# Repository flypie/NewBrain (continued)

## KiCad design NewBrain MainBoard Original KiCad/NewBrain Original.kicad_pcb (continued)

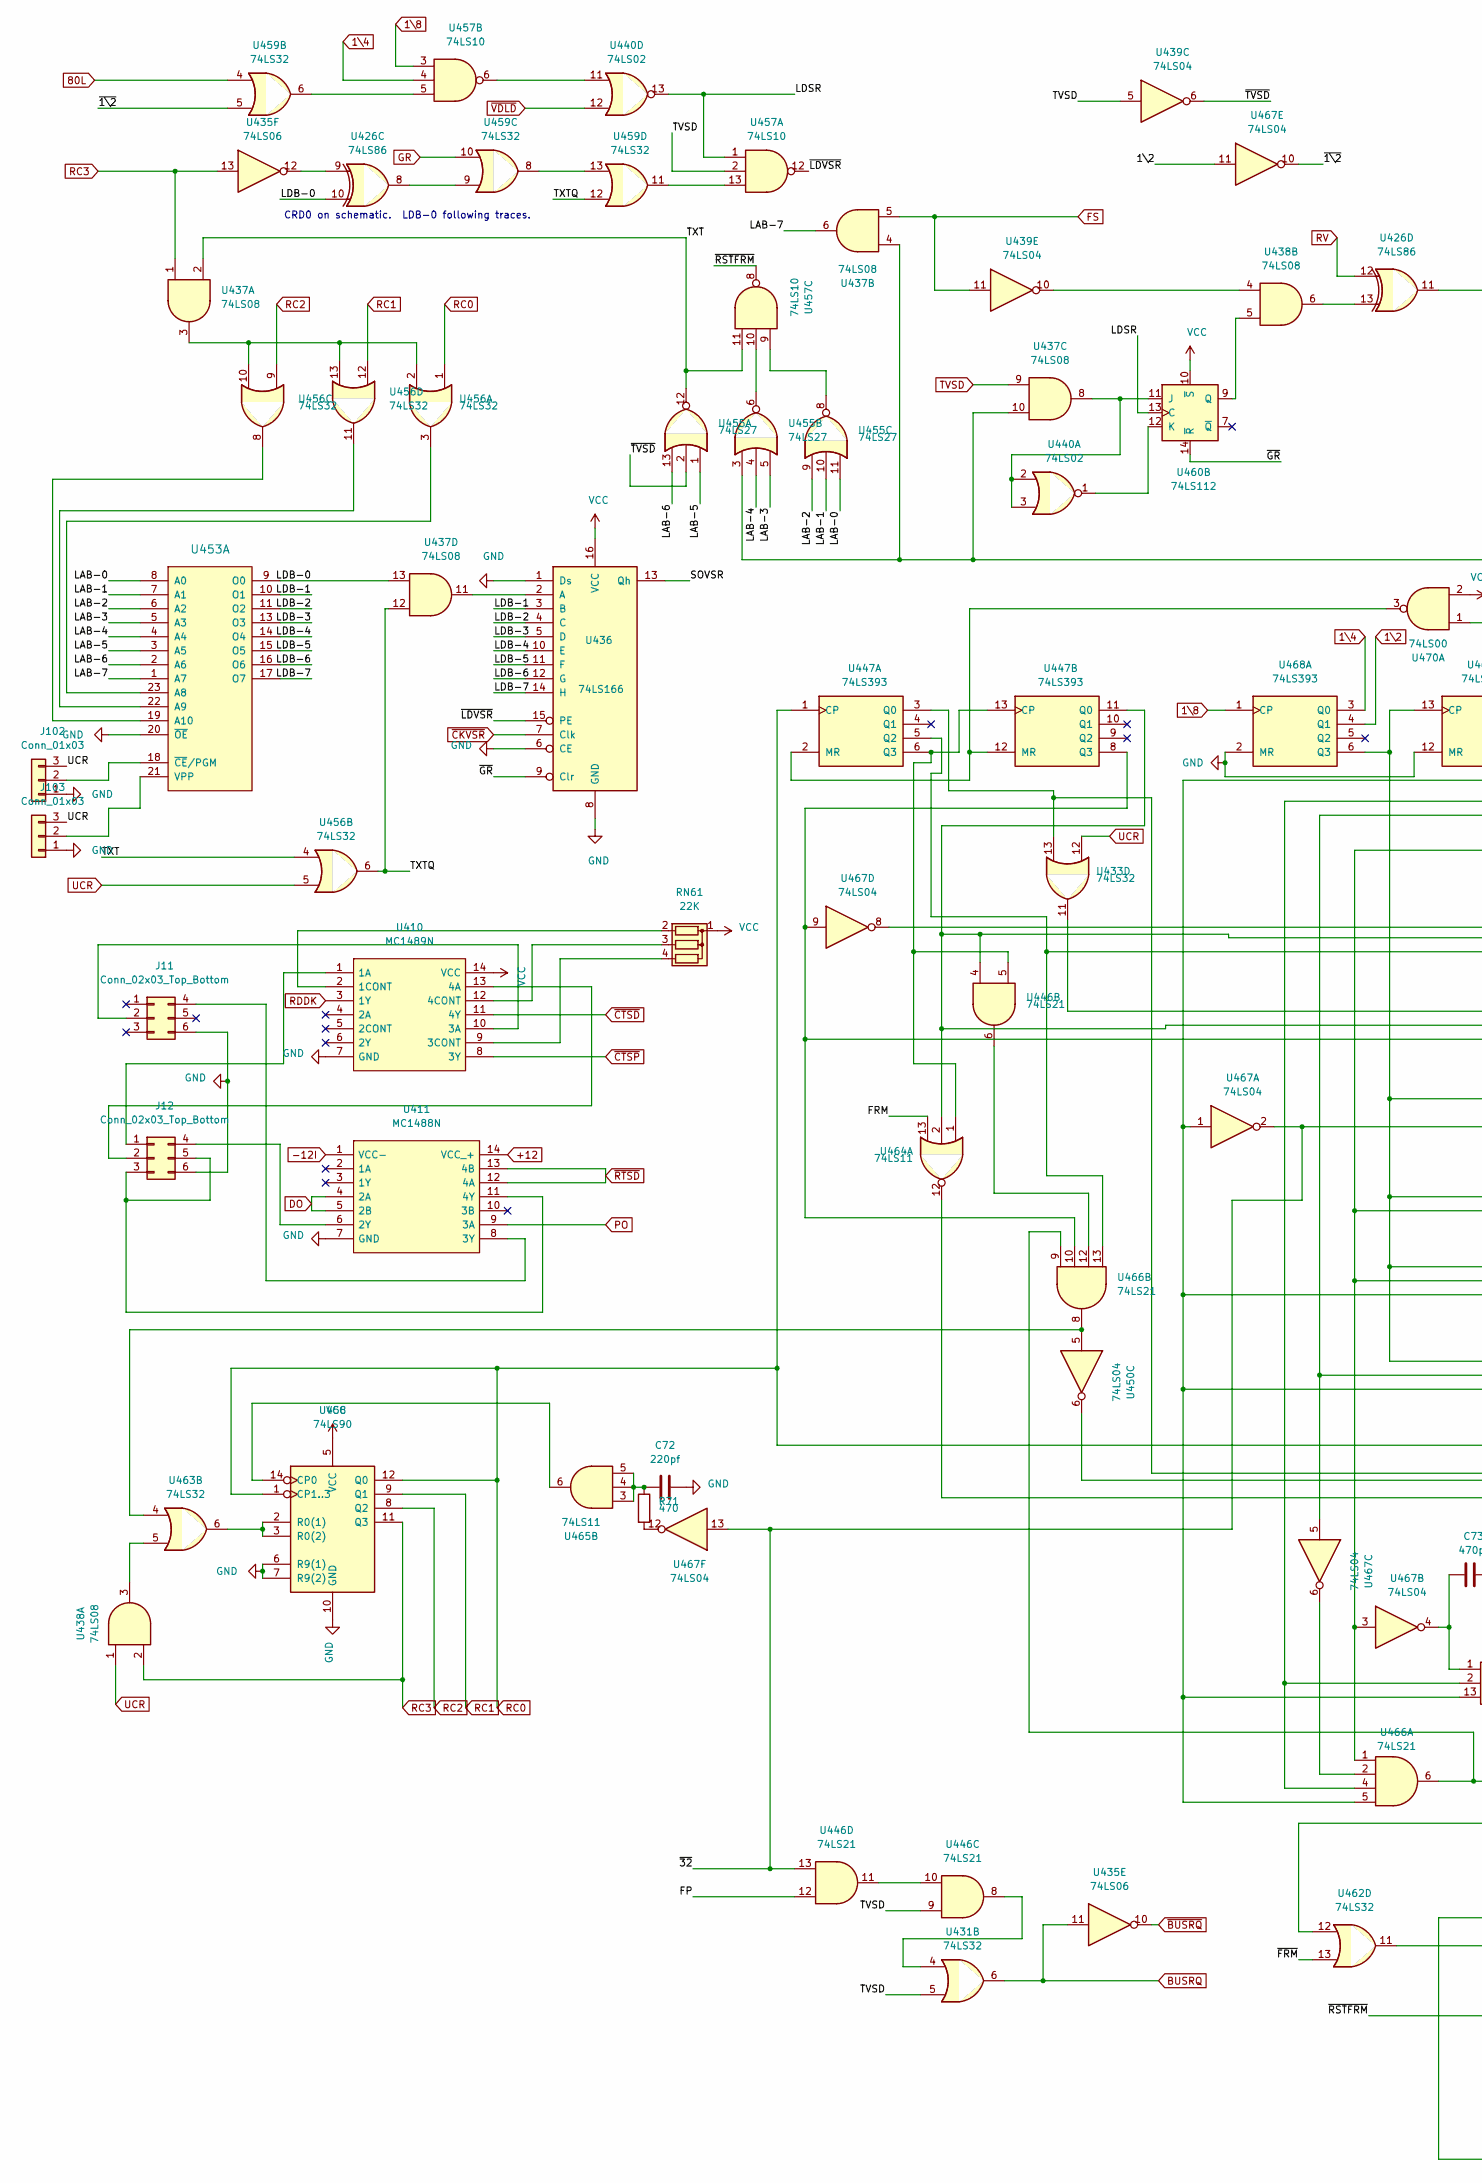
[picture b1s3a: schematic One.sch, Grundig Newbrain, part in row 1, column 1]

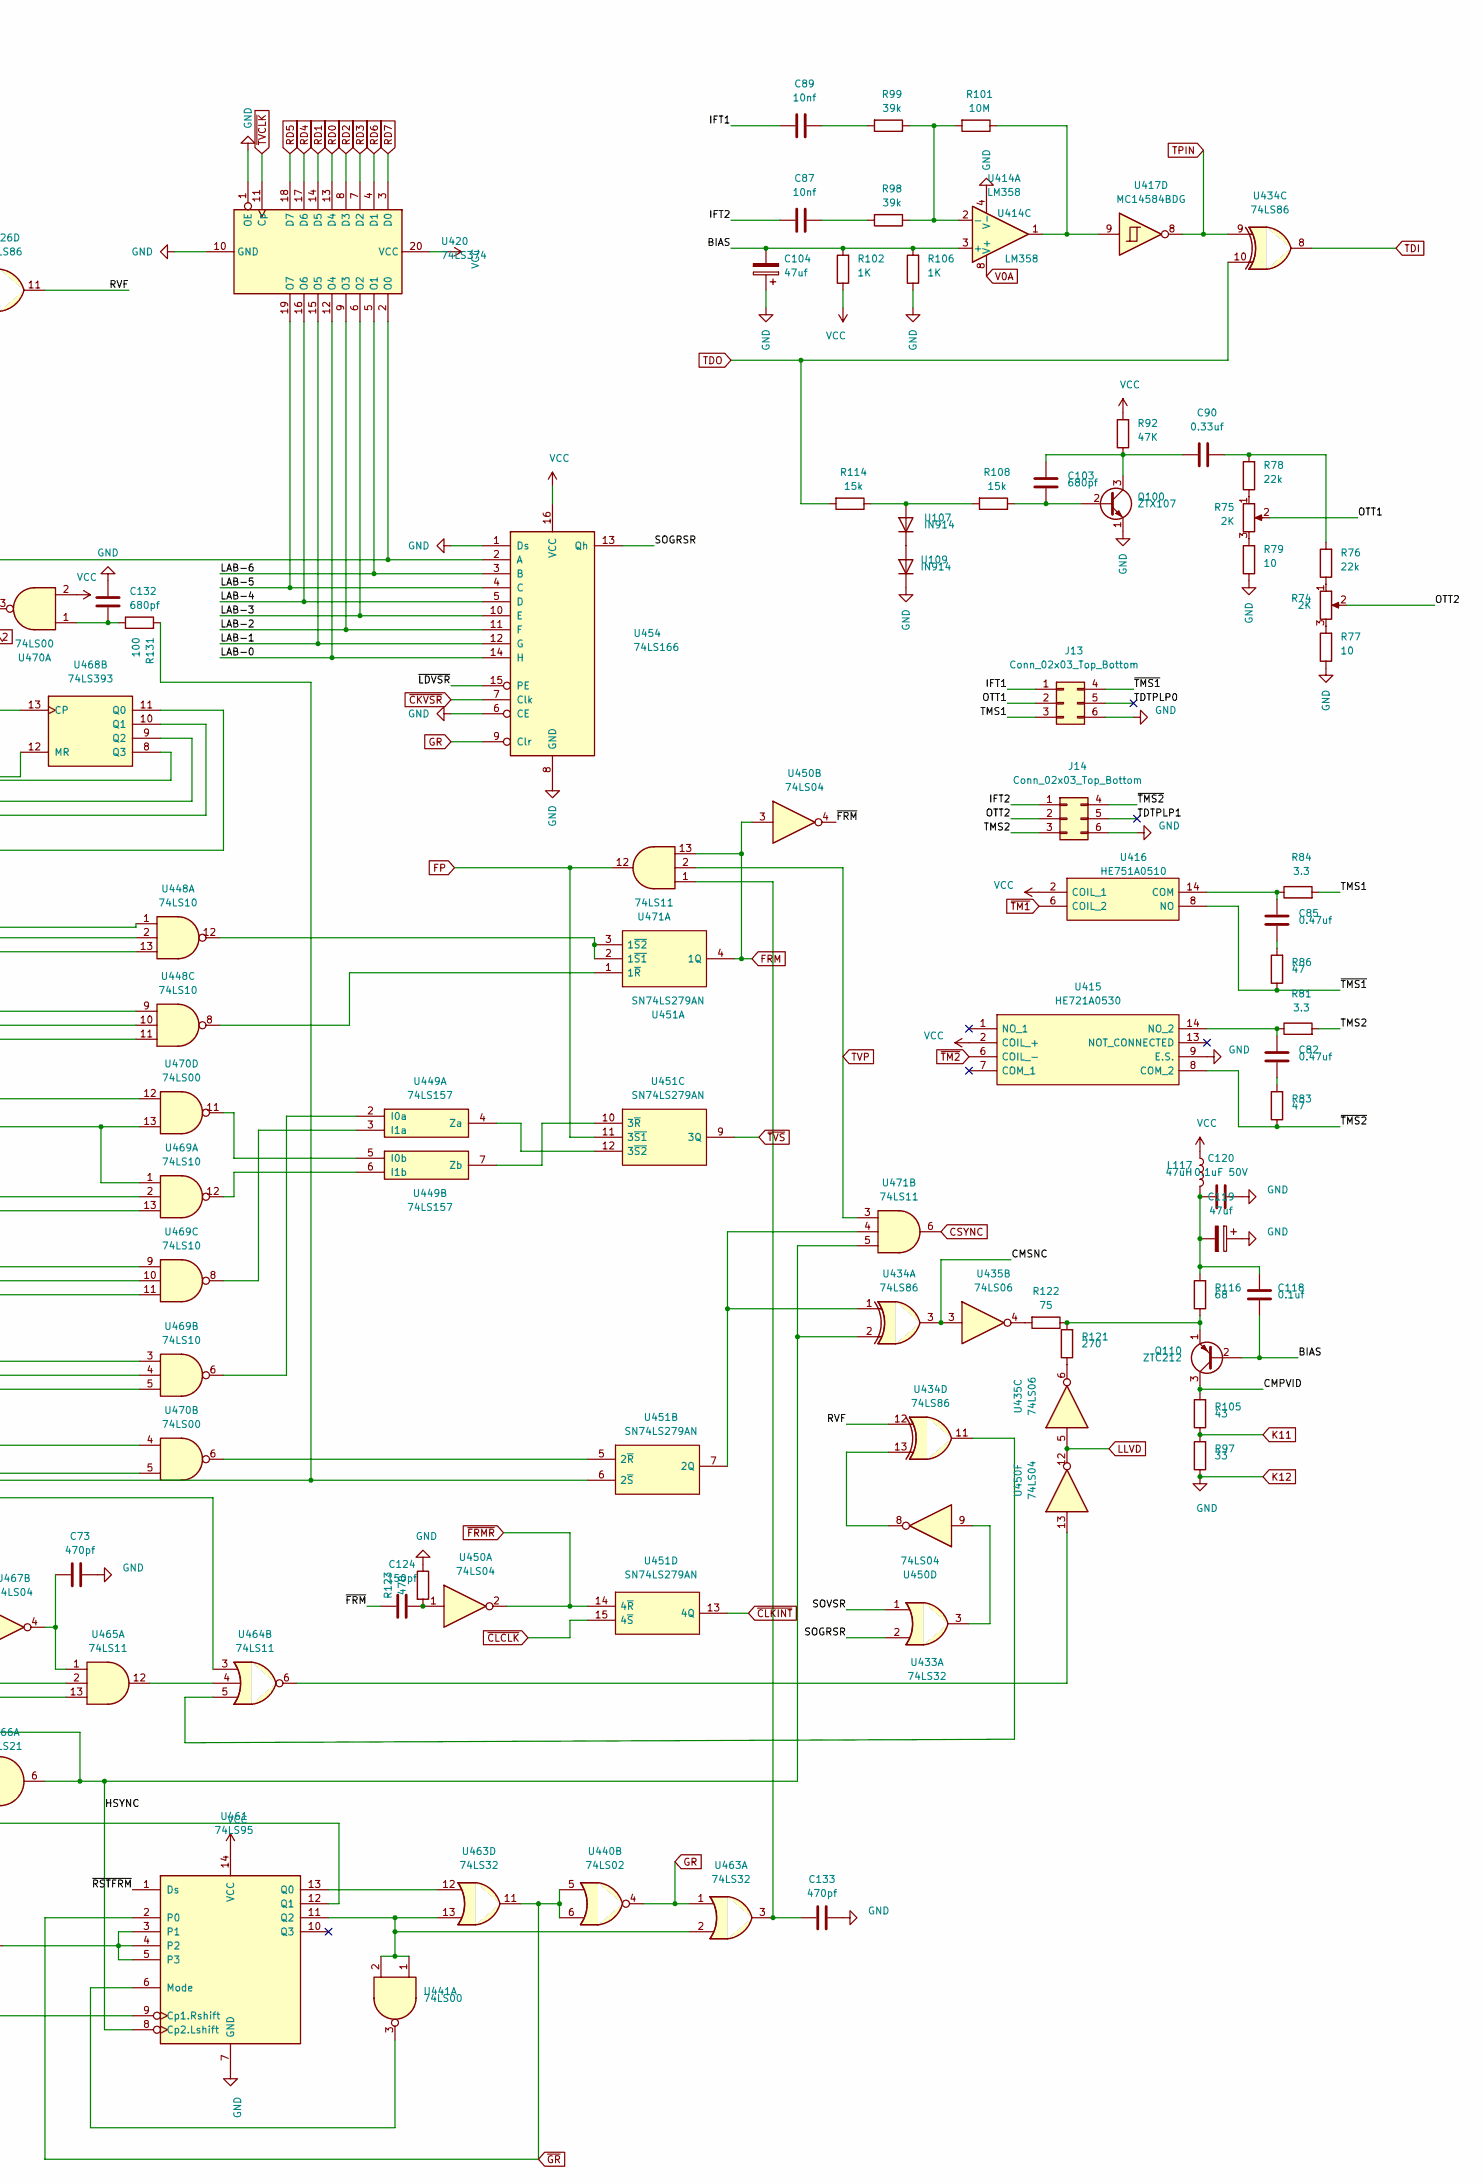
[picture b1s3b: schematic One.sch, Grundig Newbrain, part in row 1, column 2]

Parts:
C72: 220pf; C_Disc_D3.0mm_W1.6mm_P2.50mm
C73, C133: 470pf; C_Disc_D3.0mm_W1.6mm_P2.50mm
C82, C85: 0.47uf; C_Disc_D3.0mm_W1.6mm_P2.50mm
C87, C89: 10nf; C_Disc_D3.0mm_W1.6mm_P2.50mm
C90: 0.33uf; C_Disc_D3.0mm_W1.6mm_P2.50mm
C103, C132: 680pf; C_Disc_D3.0mm_W1.6mm_P2.50mm
C104, C119: 47uf; CP_Radial_D4.0mm_P1.50mm
C118: 0.1uf; C_Disc_D3.0mm_W1.6mm_P2.50mm
C120: 0.1uF 50V; C_Axial_L3.8mm_D2.6mm_P7.50mm_Horizontal
C124: 150pf; C_Disc_D3.0mm_W1.6mm_P2.50mm
J11, J12, J13, J14: Conn_02x03_Top_Bottom; PinHeader_2x03_P2.54mm_Vertical
J102, J103: Conn_01x03; PinSocket_1x03_P2.54mm_Vertical
L117: 47uH; L_Axial_L5.0mm_D3.6mm_P10.00mm_Horizontal_Murata_BL01RN1A2A2
Q100: ZTX107; TO-92_Inline
Q110: ZTC212; TO-92_Inline
R71, R123: 470; R_Axial_DIN0204_L3.6mm_D1.6mm_P1.90mm_Vertical
R74, R75: 2K; 3362H1103LF
R76, R78: 22k; R_Axial_DIN0204_L3.6mm_D1.6mm_P1.90mm_Vertical
R77, R79: 10; R_Axial_DIN0204_L3.6mm_D1.6mm_P1.90mm_Vertical
R81, R84: 3.3; R_Axial_DIN0204_L3.6mm_D1.6mm_P1.90mm_Vertical
R83, R86: 47; R_Axial_DIN0204_L3.6mm_D1.6mm_P1.90mm_Vertical
R92: 47K; R_Axial_DIN0204_L3.6mm_D1.6mm_P1.90mm_Vertical
R97: 33; R_Axial_DIN0204_L3.6mm_D1.6mm_P1.90mm_Vertical
R98, R99: 39k; R_Axial_DIN0204_L3.6mm_D1.6mm_P1.90mm_Vertical
R101: 10M; R_Axial_DIN0204_L3.6mm_D1.6mm_P1.90mm_Vertical
R102, R106: 1K; R_Axial_DIN0204_L3.6mm_D1.6mm_P1.90mm_Vertical
R105: 43; R_Axial_DIN0204_L3.6mm_D1.6mm_P1.90mm_Vertical
R108, R114: 15k; R_Axial_DIN0204_L3.6mm_D1.6mm_P1.90mm_Vertical
R116: 68; R_Axial_DIN0204_L3.6mm_D1.6mm_P1.90mm_Vertical
R121: 270; R_Axial_DIN0204_L3.6mm_D1.6mm_P1.90mm_Vertical
R122: 75; R_Axial_DIN0204_L3.6mm_D1.6mm_P1.90mm_Vertical
R131: 100; R_Axial_DIN0204_L3.6mm_D1.6mm_P1.90mm_Vertical
RN61: 22K; R_Array_SIP5
U107, U109: IN914; TO-92_Inline
U410: MC1489N; DIP794W53P254L1930H508Q14N; Manufacturer_Part_Number MC1489N; Mouser Part Number 595-MC1489N
U411: MC1488N; DIP794W53P254L1930H508Q14N; Manufacturer_Part_Number MC1488N; Mouser Part Number 595-MC1488N
U414: LM358; DIP-8_W7.62mm
U415: HE721A0530; HE721A0510; Manufacturer_Part_Number HE721A0510; Mouser Part Number 934-HE721A0510
U416: HE751A0510; Manufacturer_Part_Number HE751A0510
U417: MC14584BDG; DIP-14_W7.62mm
U420: 74LS374; DIP-20_W7.62mm
U426, U434: 74LS86; DIP-14_W7.62mm
U431, U433, U456, U459, U462, U463: 74LS32; DIP-14_W7.62mm
U435: 74LS06; DIP-14_W7.62mm
U436, U454: 74LS166; DIP-16_W7.62mm
U437, U438: 74LS08; DIP-14_W7.62mm
U439, U450, U467: 74LS04; DIP-14_W7.62mm
U440: 74LS02; DIP-14_W7.62mm
U441, U470: 74LS00; DIP-14_W7.62mm
U446, U466: 74LS21; DIP-14_W7.62mm
U447, U468: 74LS393; DIP-14_W7.62mm
U448, U457, U469: 74LS10; DIP-14_W7.62mm
U449: 74LS157; DIP-16_W7.62mm
U451: SN74LS279AN; DIP-16_W7.62mm; Mouser Part Number 595-SN74LS279AN
U453: 2716-Memory_EPROM; DIP-24_W10.16mm_LongPads
U455: 74LS27; DIP-14_W7.62mm
U458: 74LS90; DIP-14_W7.62mm
U460: 74LS112; DIP-16_W7.62mm
U461: 74LS95; DIP-14_W7.62mm
U464, U465, U471: 74LS11; DIP-14_W7.62mm

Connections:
1\2: U467.11, U468.4 (Q1); also elsewhere on the board
1\4: U457.4, U468.3 (Q0); also elsewhere on the board
1\8: U457.3, U468.1 (CP); also elsewhere on the board
80L: U459.4; also elsewhere on the board
+12: U411.14 (VCC_+); also elsewhere on the board
-12I: U411.1 (VCC-); also elsewhere on the board
/ONE/BIAS: C104.2, C118.1, Q110.2 (B), R102.2, R106.2, U414.3 (+)
/ONE/CMPVID: Q110.3 (C), R105.2
/ONE/CMSNC: U434.3, U435.3
/ONE/HSYNC: U434.2, U461.8 (Cp2.Lshift), U466.6, U466.9, U471.5
/ONE/IFT1: C89.2, J13.1
/ONE/IFT2: C87.2, J14.1
/ONE/LAB-0: U420.12 (O4), U453.8 (A0), U454.14 (H), U455.11
/ONE/LAB-1: U420.15 (O5), U453.7 (A1), U454.12 (G), U455.10
/ONE/LAB-2: U420.9 (O3), U453.6 (A2), U454.11 (F), U455.9
/ONE/LAB-3: U420.6 (O2), U453.5 (A3), U454.10 (E), U455.5
/ONE/LAB-4: U420.16 (O6), U453.4 (A4), U454.5 (D), U455.4
/ONE/LAB-5: U420.19 (O7), U453.3 (A5), U454.4 (C), U455.1
/ONE/LAB-6: U420.5 (O1), U453.2 (A6), U454.3 (B), U455.13
/ONE/LAB-7: U437.6, U453.1 (A7)
/ONE/LDB-0: U426.10, U437.13, U453.9 (O0)
/ONE/LDB-1: U436.3 (B), U453.10 (O1)
/ONE/LDB-2: U436.4 (C), U453.11 (O2)
/ONE/LDB-3: U436.5 (D), U453.13 (O3)
/ONE/LDB-4: U436.10 (E), U453.14 (O4)
/ONE/LDB-5: U436.11 (F), U453.15 (O5)
/ONE/LDB-6: U436.12 (G), U453.16 (O6)
/ONE/LDB-7: U436.14 (H), U453.17 (O7)
/ONE/LDSR: U440.13, U457.1, U460.13 (C)
/ONE/OTT1: J13.2, R75.2
/ONE/OTT2: J14.2, R74.2
/ONE/RVF: U426.11, U434.12
/ONE/SOGRSR: U433.2, U454.13 (Qh)
/ONE/SOVSR: U433.1, U436.13 (Qh)
/ONE/TDTPLP0: J13.5
/ONE/TDTPLP1: J14.5
/ONE/TMS1: J13.3, R84.2
/ONE/TMS2: J14.3, R81.2
/ONE/TXT: U437.2, U455.12, U456.4, U457.11
/ONE/TXTQ: U437.12, U456.6, U459.12
/ONE/~1\2: U459.5, U467.10
/ONE/~32: U446.13, U467.2, U467.13, U469.1, U470.13
/ONE/~FRM: C124.2, U450.4, U462.13
/ONE/~LDVSR: U436.15 (PE), U454.15 (PE), U457.12
/ONE/~RSTFRM: U457.8, U461.1 (Ds), U461.9 (Cp1.Rshift)
/ONE/~TMS1: J13.4, R86.1, U416.8 (NO)
/ONE/~TMS2: J14.4, R83.1, U415.8 (COM_2)
/ONE/~TVSD: U439.6, U455.2
BUSRQ: U431.6, U435.11; also elsewhere on the board
CSYNC: U471.6; also elsewhere on the board
DO: U411.4 (2A), U411.5 (2B); also elsewhere on the board
FP: U446.12, U451.11 (3~S1), U471.12; also elsewhere on the board
FRM: U450.3, U451.4 (1Q), U464.13, U471.13; also elsewhere on the board
FS: U437.5, U439.11; also elsewhere on the board
GR: U440.4, U454.9 (Clr), U459.10, U463.1; also elsewhere on the board
K11: R97.2, R105.1; also elsewhere on the board
K12: C72.2, C73.1, C104.1, C119.1, C120.1, C132.2, C133.1, J11.6, J12.6, J13.6, J14.6, J102.1, J103.1, Q100.1 (E), R77.1, R79.1, R97.1, R106.1, R123.1, U109.1 (K), U410.7 (GND), U411.7 (GND), U414.4 (V-), U415.9 (E.S.), U420.1 (OE), U420.10 (GND), U436.1 (Ds), U436.6 (CE), U436.8 (GND), U453.20 (~OE), U454.1 (Ds), U454.6 (CE), U454.8 (GND), U458.6 (R9(1)), U458.7 (R9(2)), U458.10 (GND), U461.7 (GND), U468.2 (MR), U468.12 (MR); also elsewhere on the board
LLVD: U435.5, U450.12; also elsewhere on the board
unnamed: C72.1, R71.1, U465.3, U465.4, U465.5
unnamed: C73.2, U465.1, U467.4
unnamed: C82.1, R83.2
unnamed: C82.2, R81.1, U415.14 (NO_2)
unnamed: C85.1, R86.2
unnamed: C85.2, R84.1, U416.14 (COM)
unnamed: C87.1, R98.2
unnamed: C89.1, R99.2
unnamed: C90.1, R76.2, R78.2
unnamed: C103.1, Q100.2 (B), R108.1
unnamed: C90.2, C103.2, Q100.3 (C), R92.1
unnamed: C118.2, C119.2, C120.2, L117.2, R116.2
unnamed: C124.1, R123.2, U450.1
unnamed: C132.1, R131.1, U470.1
unnamed: C133.2, U463.3, U471.1
unnamed: J11.2, U410.10 (3A)
unnamed: J11.4, U411.8 (3Y)
unnamed: J12.1, U410.1 (1A)
unnamed: J12.2, U410.13 (4A)
unnamed: J12.3, J12.5, U411.11 (4Y)
unnamed: J12.4, U411.6 (2Y)
unnamed: J102.2, U453.18 (~CE~/PGM)
unnamed: J103.2, U453.21 (VPP)
unnamed: Q110.1 (E), R116.1, R121.2, R122.1
unnamed: R71.2, U467.12
unnamed: R74.1, R76.1
unnamed: R74.3, R77.2
unnamed: R75.1, R78.1
unnamed: R75.3, R79.2
unnamed: R101.1, U414.1, U417.9
unnamed: R98.1, R99.1, R101.2, U414.2 (-)
unnamed: R108.2, R114.1, U107.2 (A)
unnamed: R121.1, U435.6
unnamed: R122.2, U435.4
unnamed: R131.2, U450.6, U451.6 (2~S)
unnamed: RN61.2 (R1), U410.2 (1CONT)
unnamed: RN61.3 (R2), U410.12 (4CONT)
unnamed: RN61.4 (R3), U410.9 (3CONT)
unnamed: U107.1 (K), U109.2 (A)
unnamed: U420.2 (O0), U437.4, U437.10, U454.2 (A), U455.3
unnamed: U426.8, U459.9
unnamed: U426.9, U435.12
unnamed: U426.13, U438.6
unnamed: U431.4, U446.8
unnamed: U433.3, U450.9
unnamed: U433.11, U448.9
unnamed: U433.13, U447.3 (Q0), U470.5
unnamed: U434.1, U451.7 (2Q), U471.4
unnamed: U434.11, U464.5
unnamed: U434.13, U450.8
unnamed: U436.2 (A), U437.11
unnamed: U437.3, U456.2, U456.10, U456.13
unnamed: U437.8, U440.2, U440.3, U460.11 (J)
unnamed: U438.3, U463.5
unnamed: U438.4, U439.10
unnamed: U438.5, U460.9 (Q)
unnamed: U440.1, U460.12 (K)
unnamed: U440.11, U457.6
unnamed: U441.1, U441.2, U461.11 (Q2), U463.2, U463.13
unnamed: U441.3, U461.6 (Mode)
unnamed: U446.4, U447.11 (Q0), U448.2, U448.10, U464.2
unnamed: U446.5, U447.6 (Q3), U447.13 (CP), U464.1
unnamed: U446.6, U466.12
unnamed: U446.10, U446.11
unnamed: U447.5 (Q2), U448.13, U466.13
unnamed: U447.8 (Q3), U448.11, U466.10, U467.9
unnamed: U447.2 (MR), U447.12 (MR), U470.3
unnamed: U448.1, U467.8
unnamed: U448.8, U451.1 (1~R)
unnamed: U448.12, U451.2 (1~S1), U451.3 (1~S2)
unnamed: U449.2 (I0a), U469.6
unnamed: U449.3 (I1a), U469.8
unnamed: U449.4 (Za), U451.12 (3~S2)
unnamed: U449.5 (I0b), U470.11
unnamed: U449.6 (I1b), U469.12
unnamed: U449.7 (Zb), U451.10 (3~R)
unnamed: U450.5, U463.4, U466.8
unnamed: U450.13, U464.6
unnamed: U451.5 (2~R), U470.6
unnamed: U453.19 (A10), U456.8
unnamed: U453.22 (A9), U456.11
unnamed: U453.23 (A8), U456.3
unnamed: U455.6, U457.10
unnamed: U455.8, U457.9
unnamed: U457.5, U459.6
unnamed: U457.13, U459.11
unnamed: U458.2 (R0(1)), U458.3 (R0(2)), U463.6
unnamed: U458.14 (CP0), U465.6
unnamed: U459.8, U459.13
unnamed: U461.3 (P1), U461.4 (P2), U461.5 (P3), U462.11
unnamed: U461.12 (Q1), U462.12
unnamed: U461.13 (Q0), U463.12
unnamed: U464.4, U465.12
unnamed: U464.3, U464.12
unnamed: U465.2, U466.4, U468.9 (Q2)
unnamed: U465.13, U466.5, U467.1, U468.8 (Q3), U469.5, U469.11
unnamed: U466.1, U467.3, U468.11 (Q0), U469.10, U469.13
unnamed: U466.2, U467.6
unnamed: U467.5, U468.10 (Q1), U469.4
unnamed: U468.6 (Q3), U468.13 (CP), U469.2, U469.3, U469.9, U470.12
PO: U411.9 (3A); also elsewhere on the board
RC0: U447.1 (CP), U456.1, U458.1 (CP1..3), U458.12 (Q0), U470.4; also elsewhere on the board
RC1: U456.12, U458.9 (Q1); also elsewhere on the board
RC2: U456.9, U458.8 (Q2); also elsewhere on the board
RC3: U435.13, U437.1, U438.2, U458.11 (Q3); also elsewhere on the board
RD0: U420.13 (D4); also elsewhere on the board
RD1: U420.14 (D5); also elsewhere on the board
RD2: U420.8 (D3); also elsewhere on the board
RD3: U420.7 (D2); also elsewhere on the board
RD4: U420.17 (D6); also elsewhere on the board
RD5: U420.18 (D7); also elsewhere on the board
RD6: U420.4 (D1); also elsewhere on the board
RD7: U420.3 (D0); also elsewhere on the board
RDDK: U410.3 (1Y); also elsewhere on the board
RV: U426.12; also elsewhere on the board
TDI: U434.8; also elsewhere on the board
TDO: R114.2, U434.10; also elsewhere on the board
TPIN: U417.8, U434.9; also elsewhere on the board
TVP: U471.2, U471.3; also elsewhere on the board
TVSD: U431.5, U437.9, U439.5, U446.9, U457.2; also elsewhere on the board
UCR: J102.3, J103.3, U433.12, U438.1, U456.5; also elsewhere on the board
V0A: U414.8 (V+); also elsewhere on the board
VCC: L117.1, R92.2, R102.1, RN61.1 (common), U410.14 (VCC), U415.2 (COIL_+), U416.2 (COIL_1), U420.20 (VCC), U436.16 (VCC), U454.16 (VCC), U458.5 (VCC), U460.10 (~S), U461.14 (VCC), U470.2; also elsewhere on the board
~BUSRQ: U435.10; also elsewhere on the board
~CKVSR: U436.7 (Clk), U454.7 (Clk); also elsewhere on the board
~CLCLK: U451.15 (4~S); also elsewhere on the board
~CLKINT: U451.13 (4Q); also elsewhere on the board
~CTSD: U410.11 (4Y); also elsewhere on the board
~CTSP: U410.8 (3Y); also elsewhere on the board
~FRMR: U450.2, U451.14 (4~R); also elsewhere on the board
~GR: U436.9 (Clr), U440.5, U440.6, U460.14 (~R), U461.2 (P0), U463.11; also elsewhere on the board
~RTSD: U411.12 (4A), U411.13 (4B); also elsewhere on the board
~TM1: U416.6 (COIL_2); also elsewhere on the board
~TM2: U415.6 (COIL_-); also elsewhere on the board
~TVCLK: U420.11 (Cp); also elsewhere on the board
~TVS: U451.9 (3Q); also elsewhere on the board
~VDLD: U440.12; also elsewhere on the board

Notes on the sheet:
CRD0 on schematic. LDB-0 following traces.

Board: 2 copper layers, 209 parts (0 on the bottom side), 357 nets, no tracks yet.

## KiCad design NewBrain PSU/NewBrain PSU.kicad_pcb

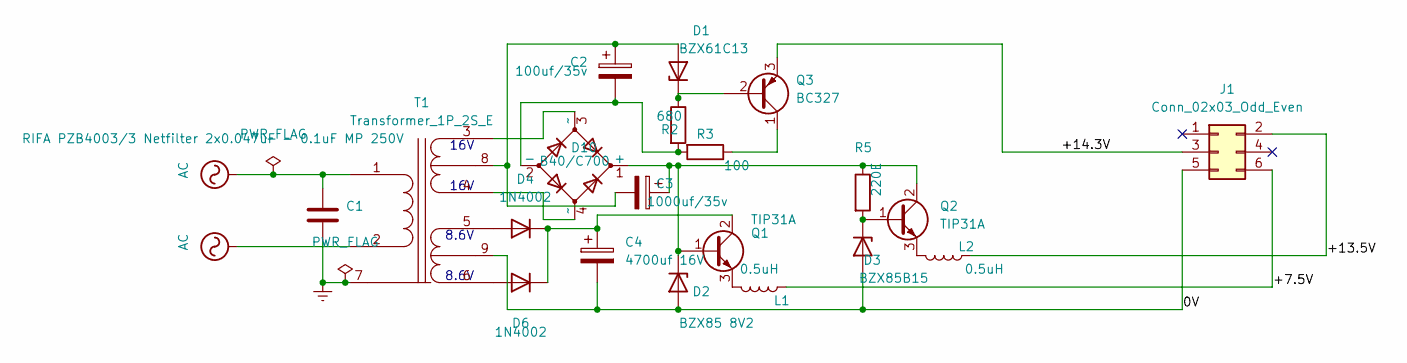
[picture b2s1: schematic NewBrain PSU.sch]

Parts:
C1: RIFA PZB4003/3 Netfilter 2x0.047uF - 0.1uF MP 250V; CP_Axial_L18.0mm_D10.0mm_P25.00mm_Horizontal
C2: 100uf/35v; CP_Radial_D5.0mm_P2.00mm
C3: 1000uf/35v; CP_Radial_D5.0mm_P2.00mm
C4: 4700uf 16V; CP_Radial_D5.0mm_P2.00mm
D1: BZX61C13; D_DO-15_P5.08mm_Vertical_AnodeUp
D2: BZX85 8V2; D_DO-15_P5.08mm_Vertical_AnodeUp
D3: BZX85B15; D_DO-15_P5.08mm_Vertical_AnodeUp
D4, D6: 1N4002; D_DO-15_P5.08mm_Vertical_AnodeUp
D10: B40/C700; Diode_Bridge_15.1x15.1x6.3mm_P10.9mm
J1: Conn_02x03_Odd_Even; PinHeader_2x03_P2.54mm_Vertical
L1, L2: 0.5uH; L_Axial_L5.0mm_D3.6mm_P10.00mm_Horizontal_Murata_BL01RN1A2A2
Q1, Q2: TIP31A; TO-220-3_Vertical
Q3: BC327; TO-92_Inline
R2: 680; R_Axial_DIN0204_L3.6mm_D1.6mm_P1.90mm_Vertical
R3: 100; R_Axial_DIN0204_L3.6mm_D1.6mm_P1.90mm_Vertical
R5: 220E; R_Axial_DIN0204_L3.6mm_D1.6mm_P1.90mm_Vertical
T1: Transformer_1P_2S_E; Transformer_CHK_EI30-2VA_2xSec

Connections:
/0V: C4.2, D2.2 (A), D3.2 (A), J1.5, T1.9 (SF)
/+7.5V: J1.6, L1.1
/+13.5V: J1.2, L2.1
/+14.3V: J1.3, Q3.3 (E)
AC: C1.1, T1.1 (AA), T1.2 (AB)
Earth: C1.2, T1.7 (EA)
unnamed: C2.1, C3.2, D1.2 (A), T1.8 (SE)
unnamed: C2.2, D10.2 (-), R2.2, R3.2
unnamed: C3.1, D2.1 (K), D10.1 (+), Q1.1 (B), Q2.2 (C), R5.1
unnamed: C4.1, D4.1 (K), D6.1 (K), Q1.2 (C)
unnamed: D1.1 (K), Q3.2 (B), R2.1
unnamed: D3.1 (K), Q2.1 (B), R5.2
unnamed: D4.2 (A), T1.5 (SC)
unnamed: D6.2 (A), T1.6 (SD)
unnamed: D10.3 (~~), T1.3 (SA)
unnamed: D10.4 (~~), T1.4 (SB)
unnamed: L1.2, Q1.3 (E)
unnamed: L2.2, Q2.3 (E)
unnamed: Q3.1 (C), R3.1

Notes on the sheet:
8.6V
16V

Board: 2 copper layers, 20 parts (0 on the bottom side), 19 nets, no tracks yet.

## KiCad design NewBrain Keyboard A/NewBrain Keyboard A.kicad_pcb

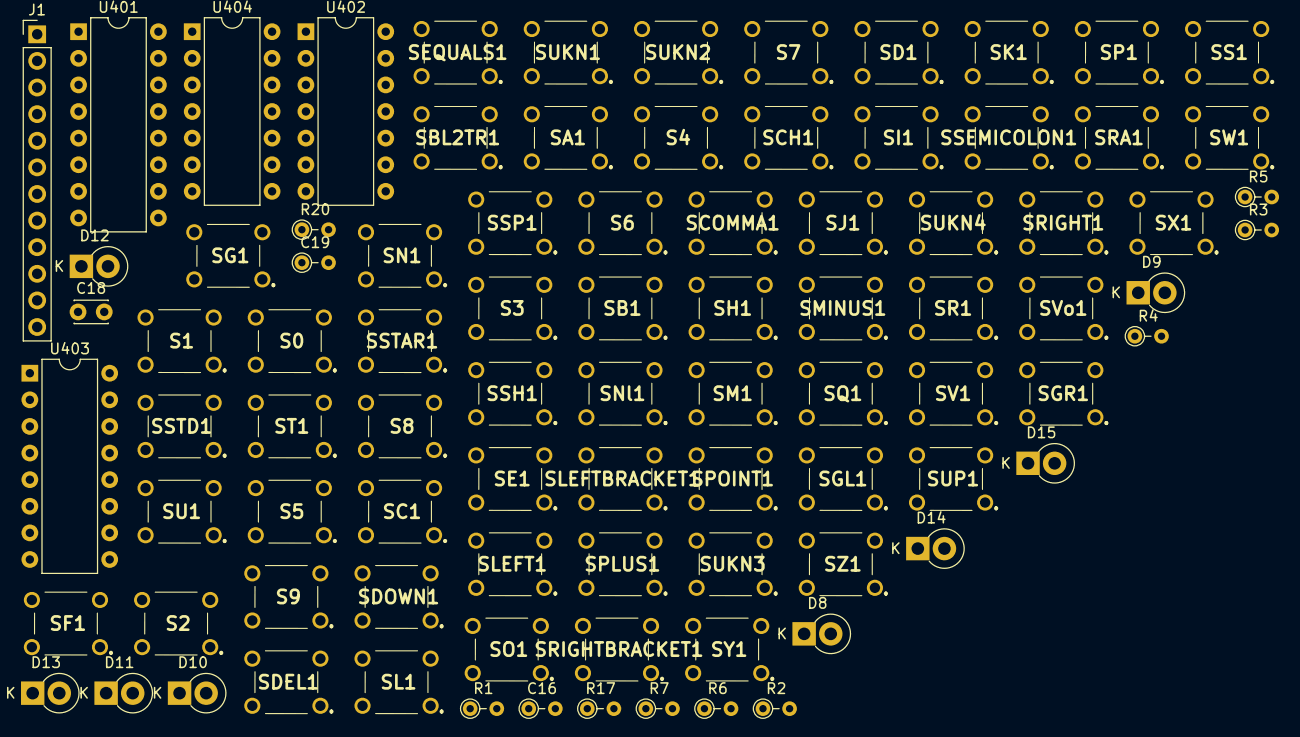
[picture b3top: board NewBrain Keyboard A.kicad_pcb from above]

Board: 2 copper layers, 89 parts (0 on the bottom side), 49 nets, no tracks yet.

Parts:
C16: 47u; R_Axial_DIN0204_L3.6mm_D1.6mm_P2.54mm_Vertical
C18: 0.1u; C_Disc_D3.0mm_W2.0mm_P2.50mm
C19: 10u; R_Axial_DIN0204_L3.6mm_D1.6mm_P2.54mm_Vertical
D8, D9, D10, D11, D12, D13, D14, D15: 1N4148; D_DO-15_P2.54mm_Vertical_KathodeUp
J1: Conn_01x12; PinHeader_1x12_P2.54mm_Vertical
R1, R3, R5, R7: 100K; R_Axial_DIN0204_L3.6mm_D1.6mm_P2.54mm_Vertical
R2, R4, R6: 4K7; R_Axial_DIN0204_L3.6mm_D1.6mm_P2.54mm_Vertical
R17: 3K9; R_Axial_DIN0204_L3.6mm_D1.6mm_P2.54mm_Vertical
R20: 10; R_Axial_DIN0204_L3.6mm_D1.6mm_P2.54mm_Vertical
S0, S1, S2, S3, S4, S5, S6, S7, S8, S9: FSM6JH
SA1: FSM6JH
SB1: FSM6JH
SBL2TR1: FSM6JH
SC1: FSM6JH
SCH1: FSM6JH
SCOMMA1: FSM6JH
SD1: FSM6JH
SDEL1: FSM6JH
SDOWN1: FSM6JH
SE1: FSM6JH
SEQUALS1: FSM6JH
SF1: FSM6JH
SG1: FSM6JH
SGL1: FSM6JH
SGR1: FSM6JH
SH1: FSM6JH
SI1: FSM6JH
SJ1: FSM6JH
SK1: FSM6JH
SL1: FSM6JH
SLEFT1: FSM6JH
SLEFTBRACKET1: FSM6JH
SM1: FSM6JH
SMINUS1: FSM6JH
SN1: FSM6JH
SNl1: FSM6JH
SO1: FSM6JH
SP1: FSM6JH
SPLUS1: FSM6JH
SPOINT1: FSM6JH
SQ1: FSM6JH
SR1: FSM6JH
SRA1: FSM6JH
SRIGHT1: FSM6JH
SRIGHTBRACKET1: FSM6JH
SS1: FSM6JH
SSEMICOLON1: FSM6JH
SSH1: FSM6JH
SSP1: FSM6JH
SSTAR1: FSM6JH
SSTD1: FSM6JH
ST1: FSM6JH
SU1: FSM6JH
SUKN1, SUKN2, SUKN3, SUKN4: FSM6JH
SUP1: FSM6JH
SV1: FSM6JH
SVo1: FSM6JH
SW1: FSM6JH
SX1: FSM6JH
SY1: FSM6JH
SZ1: FSM6JH
U401, U403: CD4051B; DIP-16_W7.62mm
U402: 40106; DIP-14_W7.62mm
U404: CD4024BE; DIP-14_W7.62mm

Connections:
/K3: J1.3, R2.1
/K4: J1.4, U404.2
/K6: J1.6, R1.2, R3.2, R5.2, R7.2, U404.1
/K7: J1.7, R4.1
/K8: J1.8, U402.12
/K9: J1.9, R6.1
/K11: J1.11, R17.1
/K12: C16.1, J1.12
GND: C18.2, C19.2, J1.10, U401.7, U401.8, U402.7, U403.7, U403.8, U404.7
unnamed: C16.2, R17.2
unnamed: C18.1, C19.1, R20.2, U402.14
unnamed: D8.1, SGR1.4
unnamed: D9.1, SA1.4, SBL2TR1.4, SD1.4, SDOWN1.4, SF1.4, SG1.4, SH1.4, SI1.4, SL1.4, SO1.4, SS1.4, SSEMICOLON1.4, SU1.4, SUKN3.4, SY1.4
unnamed: D10.1, SGL1.4
unnamed: D10.2, D14.2, R3.1, U402.3
unnamed: D11.1, SRA1.4
unnamed: D11.2, D15.2, R1.1, U402.13
unnamed: D12.1, S0.4, S8.4, S9.4, SEQUALS1.4, SLEFTBRACKET1.4, SMINUS1.4, SNl1.4, SP1.4, SPLUS1.4, SRIGHT1.4, SRIGHTBRACKET1.4, SSTAR1.4, SSTD1.4, SUKN4.4, SVo1.4
unnamed: D8.2, D12.2, R7.1, U402.9
unnamed: D13.1, SSH1.4
unnamed: D9.2, D13.2, R5.1, U402.11
unnamed: D14.1, SB1.4, SC1.4, SCH1.4, SCOMMA1.4, SDEL1.4, SJ1.4, SK1.4, SM1.4, SN1.4, SPOINT1.4, SUKN1.4, SUP1.4, SV1.4, SX1.4, SZ1.4
unnamed: D15.1, S1.4, S2.4, S3.4, S4.4, S5.4, S6.4, S7.4, SE1.4, SLEFT1.4, SQ1.4, SR1.4, SSP1.4, ST1.4, SUKN2.4, SW1.4
unnamed: R2.2, U402.4
unnamed: R4.2, U402.10
unnamed: R6.2, U402.8
unnamed: S0.1, S0.2, S5.1, S5.2, SM1.1, SM1.2, SY1.1, SY1.2, U403.1
unnamed: S1.1, S1.2, SH1.1, SH1.2, SV1.1, SV1.2, SVo1.1, SVo1.2, U401.13
unnamed: S2.1, S2.2, SB1.1, SB1.2, SSEMICOLON1.1, SSEMICOLON1.2, SSTAR1.1, SSTAR1.2, U403.4
unnamed: S3.1, S3.2, SL1.1, SL1.2, SPOINT1.1, SPOINT1.2, SRIGHTBRACKET1.1, SRIGHTBRACKET1.2, U403.2
unnamed: S4.1, S4.2, SCOMMA1.1, SCOMMA1.2, SLEFTBRACKET1.1, SLEFTBRACKET1.2, SO1.1, SO1.2, U403.5
unnamed: S6.1, S6.2, S9.1, S9.2, SI1.1, SI1.2, SN1.1, SN1.2, U403.12
unnamed: S7.1, S7.2, S8.1, S8.2, SJ1.1, SJ1.2, SU1.1, SU1.2, U403.15
unnamed: SA1.1, SA1.2, SK1.1, SK1.2, SNl1.1, SNl1.2, SQ1.1, SQ1.2, U401.5
unnamed: SBL2TR1.2, SCH1.2, SSP1.2, SUKN4.2, U401.2
unnamed: SC1.1, SC1.2, SG1.1, SG1.2, SP1.1, SP1.2, ST1.1, ST1.2, U401.14
unnamed: SD1.1, SD1.2, SE1.1, SE1.2, SMINUS1.1, SMINUS1.2, SZ1.1, SZ1.2, U401.12
unnamed: SDEL1.1, SDEL1.2, SPLUS1.1, SPLUS1.2, SS1.1, SS1.2, SW1.1, SW1.2, U401.1
unnamed: SDOWN1.1, SDOWN1.2, SLEFT1.1, SLEFT1.2, SRIGHT1.1, SRIGHT1.2, SUP1.1, SUP1.2, U403.14
unnamed: SEQUALS1.1, SEQUALS1.2, SF1.1, SF1.2, SR1.1, SR1.2, SX1.1, SX1.2, U401.15
unnamed: SGL1.2, SGR1.2, SRA1.2, SSH1.2, U401.4
unnamed: SSTD1.1, SSTD1.2, SUKN1.1, SUKN1.2, SUKN2.1, SUKN2.2, SUKN3.1, SUKN3.2, U403.13
unnamed: U401.3, U403.3
unnamed: U401.6, U402.2
unnamed: U401.9, U403.9, U404.9
unnamed: U401.10, U403.10, U404.11
unnamed: U401.11, U403.11, U404.12
unnamed: U402.1, U403.6, U404.6
VCC: J1.5, R20.1, U401.16, U403.16, U404.14
